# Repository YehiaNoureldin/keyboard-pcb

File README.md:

# keyboard-pcb

A from-scratch 61-key mechanical keyboard: custom PCB designed in KiCad, a Raspberry Pi Pico as the controller, and firmware written by hand in C.

**Goals:** learn PCB layout fundamentals, then firmware fundamentals (GPIO, matrix scanning, debouncing, USB HID, layers).

## Repository structure
```
keyboard-pcb/
├── hardware/      KiCad 9 project: schematic, PCB, libraries, 3D models
├── firmware/      C firmware (Pico SDK), in progress
└── docs/          Design log and design reviews
```

## Hardware at a glance
- ANSI 60% layout, 61 keys, 5 × 14 matrix with one diode per key
- MX hot-swap sockets, Raspberry Pi Pico mounted on the PCB
- 2-layer board, 344.6 × 135 mm, 6 × M3 mounting holes for a 3D-printed case

Details: [`hardware/README.md`](hardware/README.md)

## Status
- [x] Schematic
- [x] Placement: switches flipped (sockets on bottom), diodes under each switch
- [ ] Routing (rows and columns)
- [ ] DRC clean, order PCBs
- [ ] 3D-printed case and switch plate
- [ ] Firmware ([roadmap](firmware/README.md))

## Documentation
- [Design log](docs/design-log.md): every design change and the reasoning behind it
- [Design review, 2026-10-27](docs/design-review-2026-10-27.md)

## Credits
Switch footprints and the socket 3D model are from [ai03's MX_V2 library](https://github.com/ai03-2725/MX_V2) (MIT License).

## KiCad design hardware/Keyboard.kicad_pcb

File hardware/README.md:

# Hardware

KiCad 9 project for the keyboard PCB.

## Opening the project
Open `Keyboard.kicad_pro` in KiCad 9. Everything the project needs is in this folder:

| Path | Contents |
| --- | --- |
| `Keyboard.kicad_sch` | Schematic: 5 × 14 key matrix, diodes, Raspberry Pi Pico |
| `Keyboard.kicad_pcb` | PCB layout (2-layer) |
| `fp-lib-table`, `sym-lib-table` | Project library tables (paths relative to this folder) |
| `lib/FootprintLibrary.pretty/` | Footprints: MX hot-swap switches (1U–6.25U), Raspberry Pi Pico |
| `lib/KeyboardSymbolLibrary.kicad_sym` | Raspberry Pi Pico symbol |
| `lib/3d/` | 3D models used by the footprints |

## Board summary
- 61 keys, ANSI 60% layout, 5 × 14 matrix, one SOD-123 diode per key (current flows row → column)
- MX hot-swap sockets and diodes on the bottom side (B.Cu); switches and Pico on top
- Board outline 344.6 × 135 mm, 6 × M3 mounting holes
- 2 layers, 0.2 mm tracks, 0.6 / 0.3 mm vias

## Pin map
| Signal | Pico pins |
| --- | --- |
| Rows 1–5 | GP1–GP5 |
| Columns 1–12 | GP11–GP22 |
| Columns 13–14 | GP26, GP27 |
| Free | GP0, GP6–GP10, GP28 |

## Before ordering
1. Run the design rules check (Inspect → Design Rules Checker) with zero errors.
2. Check the 3D viewer (Alt+3): sockets and diodes on the bottom, switches and Pico on top.
3. Export Gerbers and the drill file into a `gerbers/` folder (git-ignored).

## Credits
Switch footprints and the hot-swap socket 3D model are from [ai03's MX_V2 library](https://github.com/ai03-2725/MX_V2) (MIT License).

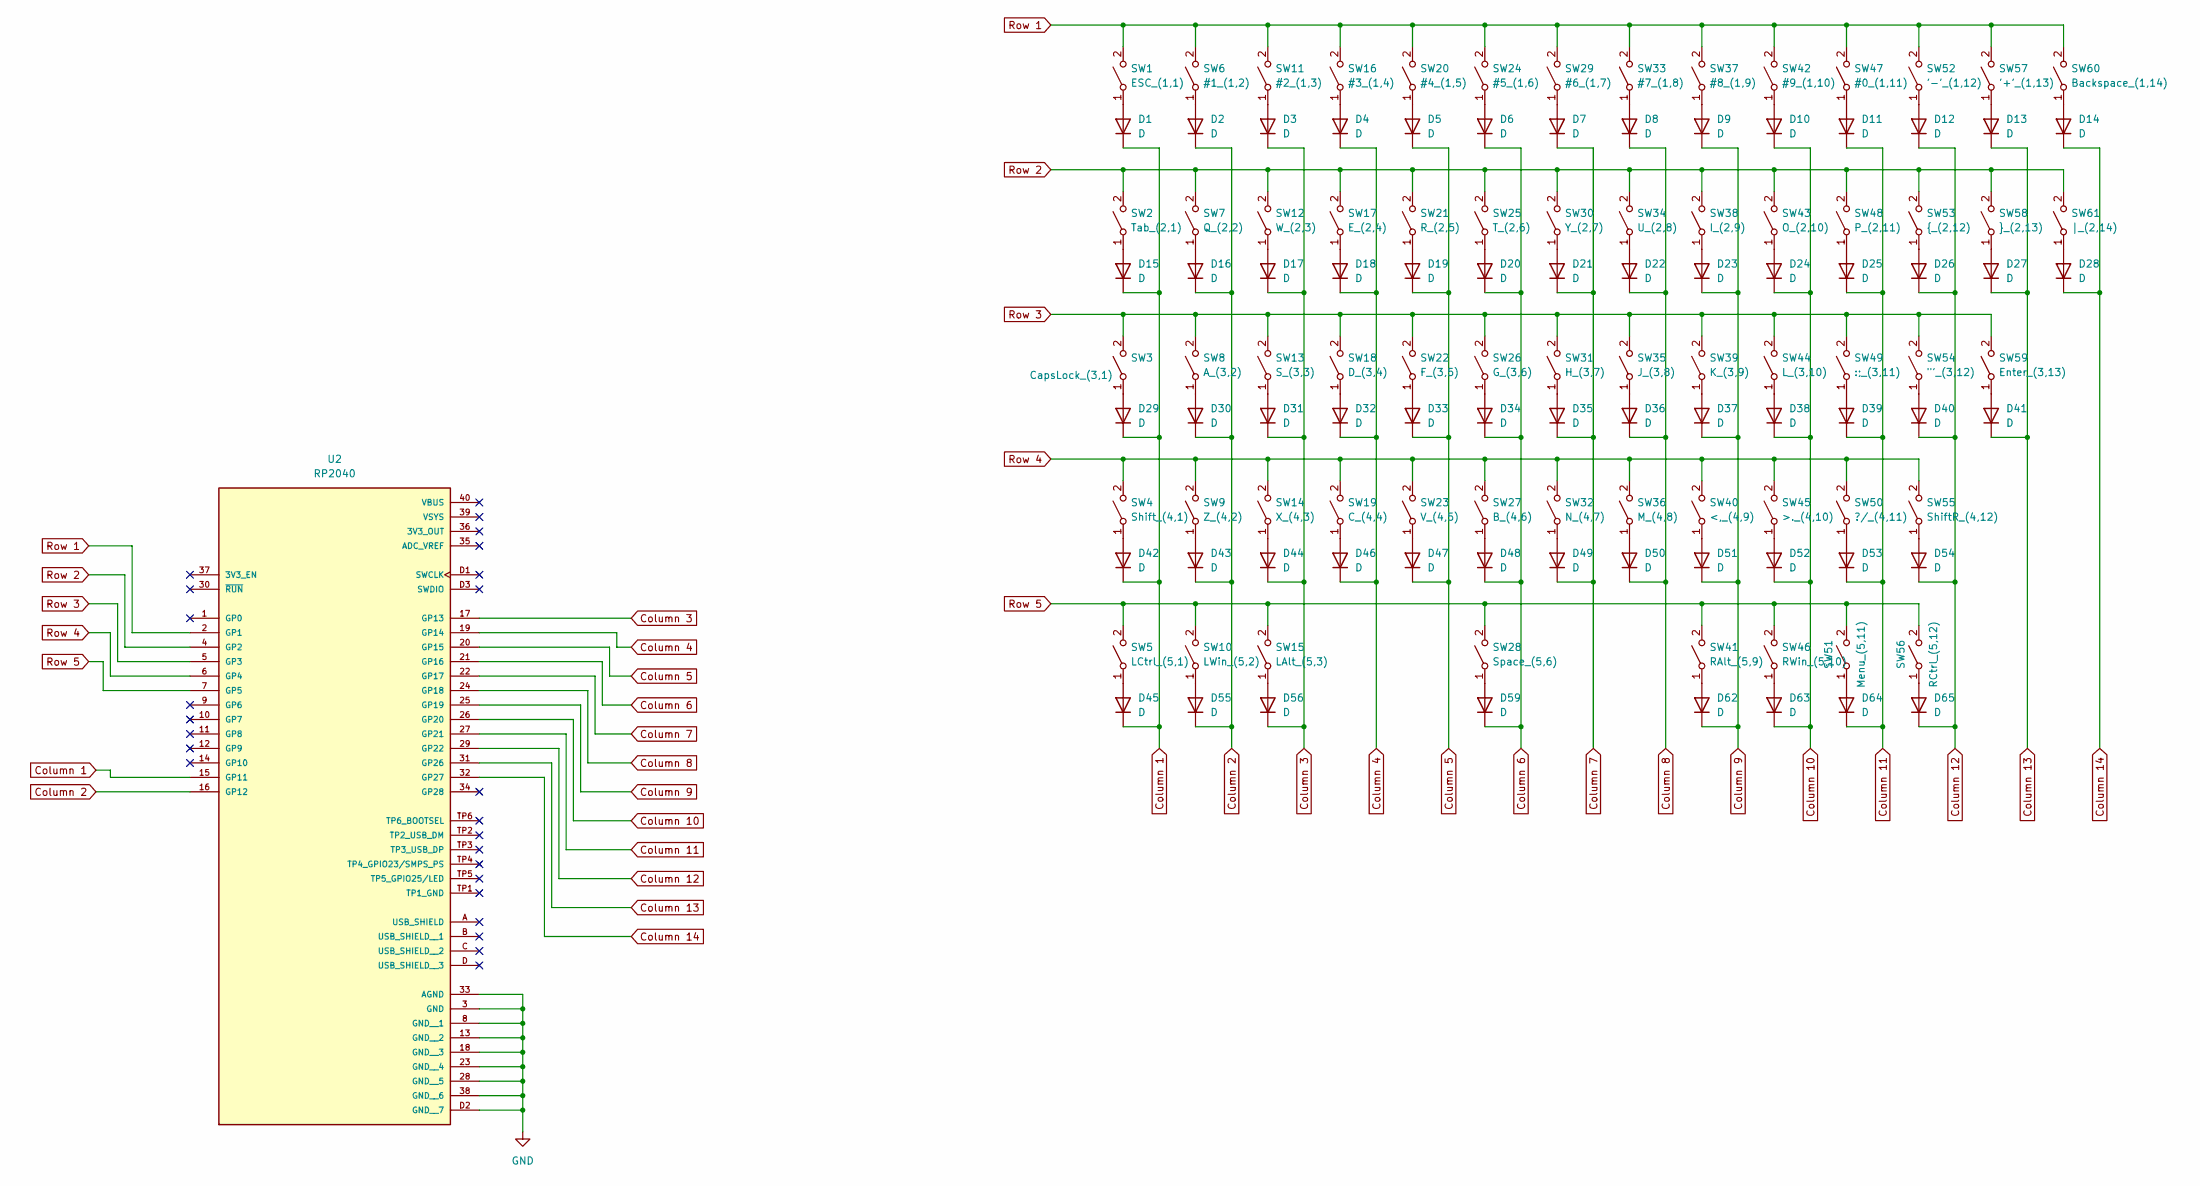
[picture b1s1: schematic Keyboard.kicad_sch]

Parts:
D1, D2, D3, D4, D5, D6, D7, D8, D9, D10, D11, D12, D13, D14, D15, D16, D17, D18, D19, D20, D21, D22, D23, D24, D25, D26, D27, D28, D29, D30, D31, D32, D33, D34, D35, D36, D37, D38, D39, D40, D41, D42, D43, D44, D45, D46, D47, D48, D49, D50, D51, D52, D53, D54, D55, D56, D59, D62, D63, D64, D65: D; D_SOD-123
SW1: ESC_(1,1); MX-Hotswap-1U
SW2: Tab_(2,1); MX-Hotswap-1.5U
SW3: CapsLock_(3,1); MX-Hotswap-1.75U
SW4: Shift_(4,1); MX-Hotswap-2.25U
SW5: LCtrl_(5,1); MX-Hotswap-1.25U
SW6: #1_(1,2); MX-Hotswap-1U
SW7: Q_(2,2); MX-Hotswap-1U
SW8: A_(3,2); MX-Hotswap-1U
SW9: Z_(4,2); MX-Hotswap-1U
SW10: LWin_(5,2); MX-Hotswap-1.25U
SW11: #2_(1,3); MX-Hotswap-1U
SW12: W_(2,3); MX-Hotswap-1U
SW13: S_(3,3); MX-Hotswap-1U
SW14: X_(4,3); MX-Hotswap-1U
SW15: LAlt_(5,3); MX-Hotswap-1.25U
SW16: #3_(1,4); MX-Hotswap-1U
SW17: E_(2,4); MX-Hotswap-1U
SW18: D_(3,4); MX-Hotswap-1U
SW19: C_(4,4); MX-Hotswap-1U
SW20: #4_(1,5); MX-Hotswap-1U
SW21: R_(2,5); MX-Hotswap-1U
SW22: F_(3,5); MX-Hotswap-1U
SW23: V_(4,5); MX-Hotswap-1U
SW24: #5_(1,6); MX-Hotswap-1U
SW25: T_(2,6); MX-Hotswap-1U
SW26: G_(3,6); MX-Hotswap-1U
SW27: B_(4,6); MX-Hotswap-1U
SW28: Space_(5,6); MX-Hotswap-6.25U
SW29: #6_(1,7); MX-Hotswap-1U
SW30: Y_(2,7); MX-Hotswap-1U
SW31: H_(3,7); MX-Hotswap-1U
SW32: N_(4,7); MX-Hotswap-1U
SW33: #7_(1,8); MX-Hotswap-1U
SW34: U_(2,8); MX-Hotswap-1U
SW35: J_(3,8); MX-Hotswap-1U
SW36: M_(4,8); MX-Hotswap-1U
SW37: #8_(1,9); MX-Hotswap-1U
SW38: I_(2,9); MX-Hotswap-1U
SW39: K_(3,9); MX-Hotswap-1U
SW40: <,_(4,9); MX-Hotswap-1U
SW41: RAlt_(5,9); MX-Hotswap-1.25U
SW42: #9_(1,10); MX-Hotswap-1U
SW43: O_(2,10); MX-Hotswap-1U
SW44: L_(3,10); MX-Hotswap-1U
SW45: >._(4,10); MX-Hotswap-1U
SW46: RWin_(5,10); MX-Hotswap-1.25U
SW47: #0_(1,11); MX-Hotswap-1U
SW48: P_(2,11); MX-Hotswap-1U
SW49: :;_(3,11); MX-Hotswap-1U
SW50: ?/_(4,11); MX-Hotswap-1U
SW51: Menu_(5,11); MX-Hotswap-1.25U
SW52: '-'_(1,12); MX-Hotswap-1U
SW53: {_(2,12); MX-Hotswap-1U
SW54: "'_(3,12); MX-Hotswap-1U
SW55: ShiftR_(4,12); MX-Hotswap-2.75U
SW56: RCtrl_(5,12); MX-Hotswap-1.25U
SW57: '+'_(1,13); MX-Hotswap-1U
SW58: }_(2,13); MX-Hotswap-1U
SW59: Enter_(3,13); MX-Hotswap-2.25U
SW60: Backspace_(1,14); MX-Hotswap-2U
SW61: |_(2,14); MX-Hotswap-1.5U
U2: RP2040; RP2040 Pico; PARTREV 1.9

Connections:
Column 1: D1.1 (K), D15.1 (K), D29.1 (K), D42.1 (K), D45.1 (K), U2.15 (GP11)
Column 2: D2.1 (K), D16.1 (K), D30.1 (K), D43.1 (K), D55.1 (K), U2.16 (GP12)
Column 3: D3.1 (K), D17.1 (K), D31.1 (K), D44.1 (K), D56.1 (K), U2.17 (GP13)
Column 4: D4.1 (K), D18.1 (K), D32.1 (K), D46.1 (K), U2.19 (GP14)
Column 5: D5.1 (K), D19.1 (K), D33.1 (K), D47.1 (K), U2.20 (GP15)
Column 6: D6.1 (K), D20.1 (K), D34.1 (K), D48.1 (K), D59.1 (K), U2.21 (GP16)
Column 7: D7.1 (K), D21.1 (K), D35.1 (K), D49.1 (K), U2.22 (GP17)
Column 8: D8.1 (K), D22.1 (K), D36.1 (K), D50.1 (K), U2.24 (GP18)
Column 9: D9.1 (K), D23.1 (K), D37.1 (K), D51.1 (K), D62.1 (K), U2.25 (GP19)
Column 10: D10.1 (K), D24.1 (K), D38.1 (K), D52.1 (K), D63.1 (K), U2.26 (GP20)
Column 11: D11.1 (K), D25.1 (K), D39.1 (K), D53.1 (K), D64.1 (K), U2.27 (GP21)
Column 12: D12.1 (K), D26.1 (K), D40.1 (K), D54.1 (K), D65.1 (K), U2.29 (GP22)
Column 13: D13.1 (K), D27.1 (K), D41.1 (K), U2.31 (GP26)
Column 14: D14.1 (K), D28.1 (K), U2.32 (GP27)
GND: U2.3 (GND), U2.8 (GND__1), U2.13 (GND__2), U2.18 (GND__3), U2.23 (GND__4), U2.28 (GND__5), U2.33 (AGND), U2.38 (GND__6), U2.D2 (GND__7)
unnamed: D1.2 (A), SW1.1 (A)
unnamed: D2.2 (A), SW6.1 (A)
unnamed: D3.2 (A), SW11.1 (A)
unnamed: D4.2 (A), SW16.1 (A)
unnamed: D5.2 (A), SW20.1 (A)
unnamed: D6.2 (A), SW24.1 (A)
unnamed: D7.2 (A), SW29.1 (A)
unnamed: D8.2 (A), SW33.1 (A)
unnamed: D9.2 (A), SW37.1 (A)
unnamed: D10.2 (A), SW42.1 (A)
unnamed: D11.2 (A), SW47.1 (A)
unnamed: D12.2 (A), SW52.1 (A)
unnamed: D13.2 (A), SW57.1 (A)
unnamed: D14.2 (A), SW60.1 (A)
unnamed: D15.2 (A), SW2.1 (A)
unnamed: D16.2 (A), SW7.1 (A)
unnamed: D17.2 (A), SW12.1 (A)
unnamed: D18.2 (A), SW17.1 (A)
unnamed: D19.2 (A), SW21.1 (A)
unnamed: D20.2 (A), SW25.1 (A)
unnamed: D21.2 (A), SW30.1 (A)
unnamed: D22.2 (A), SW34.1 (A)
unnamed: D23.2 (A), SW38.1 (A)
unnamed: D24.2 (A), SW43.1 (A)
unnamed: D25.2 (A), SW48.1 (A)
unnamed: D26.2 (A), SW53.1 (A)
unnamed: D27.2 (A), SW58.1 (A)
unnamed: D28.2 (A), SW61.1 (A)
unnamed: D29.2 (A), SW3.1 (A)
unnamed: D30.2 (A), SW8.1 (A)
unnamed: D31.2 (A), SW13.1 (A)
unnamed: D32.2 (A), SW18.1 (A)
unnamed: D33.2 (A), SW22.1 (A)
unnamed: D34.2 (A), SW26.1 (A)
unnamed: D35.2 (A), SW31.1 (A)
unnamed: D36.2 (A), SW35.1 (A)
unnamed: D37.2 (A), SW39.1 (A)
unnamed: D38.2 (A), SW44.1 (A)
unnamed: D39.2 (A), SW49.1 (A)
unnamed: D40.2 (A), SW54.1 (A)
unnamed: D41.2 (A), SW59.1 (A)
unnamed: D42.2 (A), SW4.1 (A)
unnamed: D43.2 (A), SW9.1 (A)
unnamed: D44.2 (A), SW14.1 (A)
unnamed: D45.2 (A), SW5.1 (A)
unnamed: D46.2 (A), SW19.1 (A)
unnamed: D47.2 (A), SW23.1 (A)
unnamed: D48.2 (A), SW27.1 (A)
unnamed: D49.2 (A), SW32.1 (A)
unnamed: D50.2 (A), SW36.1 (A)
unnamed: D51.2 (A), SW40.1 (A)
unnamed: D52.2 (A), SW45.1 (A)
unnamed: D53.2 (A), SW50.1 (A)
unnamed: D54.2 (A), SW55.1 (A)
unnamed: D55.2 (A), SW10.1 (A)
unnamed: D56.2 (A), SW15.1 (A)
unnamed: D59.2 (A), SW28.1 (A)
unnamed: D62.2 (A), SW41.1 (A)
unnamed: D63.2 (A), SW46.1 (A)
unnamed: D64.2 (A), SW51.1 (A)
unnamed: D65.2 (A), SW56.1 (A)
Row 1: SW1.2 (B), SW6.2 (B), SW11.2 (B), SW16.2 (B), SW20.2 (B), SW24.2 (B), SW29.2 (B), SW33.2 (B), SW37.2 (B), SW42.2 (B), SW47.2 (B), SW52.2 (B), SW57.2 (B), SW60.2 (B), U2.2 (GP1)
Row 2: SW2.2 (B), SW7.2 (B), SW12.2 (B), SW17.2 (B), SW21.2 (B), SW25.2 (B), SW30.2 (B), SW34.2 (B), SW38.2 (B), SW43.2 (B), SW48.2 (B), SW53.2 (B), SW58.2 (B), SW61.2 (B), U2.4 (GP2)
Row 3: SW3.2 (B), SW8.2 (B), SW13.2 (B), SW18.2 (B), SW22.2 (B), SW26.2 (B), SW31.2 (B), SW35.2 (B), SW39.2 (B), SW44.2 (B), SW49.2 (B), SW54.2 (B), SW59.2 (B), U2.5 (GP3)
Row 4: SW4.2 (B), SW9.2 (B), SW14.2 (B), SW19.2 (B), SW23.2 (B), SW27.2 (B), SW32.2 (B), SW36.2 (B), SW40.2 (B), SW45.2 (B), SW50.2 (B), SW55.2 (B), U2.6 (GP4)
Row 5: SW5.2 (B), SW10.2 (B), SW15.2 (B), SW28.2 (B), SW41.2 (B), SW46.2 (B), SW51.2 (B), SW56.2 (B), U2.7 (GP5)

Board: 2 copper layers, 123 parts (122 on the bottom side), 81 nets, no tracks yet.
